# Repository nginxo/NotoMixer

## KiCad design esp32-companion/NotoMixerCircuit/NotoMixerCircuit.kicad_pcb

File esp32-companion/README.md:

# NotoMixer Companion per ESP32-S3

Firmware Arduino per ESP32-S3 N16R8 e ILI9488 SPI. Mostra entrambe le deck con titolo, BPM, tempo, stato di riproduzione, una finestra scorrevole di 8 secondi e la panoramica del brano. Le waveform arrivano da NotoMixer attraverso la porta COM USB. Le ampiezze di bassi, medi e alti sono disegnate a strati in blu, arancio e avorio. La finestra scorrevole mostra la griglia dei beat e il numero di battuta. Hot cue e loop attivi sono visibili anche nella panoramica.

## Collegamenti

| Display | ESP32-S3 |
| --- | --- |
| VDD | 3V3, se previsto dal modulo |
| GND | GND |
| CS | GPIO 10 |
| RST | GPIO 9 |
| D/C | GPIO 8 |
| SDI / MOSI | GPIO 11 |
| SCK | GPIO 12 |
| SDO / MISO | GPIO 13, facoltativo per il display in sola scrittura |
| BL | GPIO 7, attivo HIGH sul modulo provato |

Il preset riproduce il cablaggio e l'accensione dello sketch provato. GPIO 7 viene tenuto a LOW durante l'inizializzazione del pannello e portato a HIGH subito dopo. Su un modulo diverso verifica i requisiti di VDD e BL. Tutte le impostazioni del display sono in [Config.h](NotoMixerCompanion/Config.h).

Il preset usa SPI2 in modalità 0 e rotazione 1 (480 × 320 in orizzontale). Usa rotazione 3 per girare lo schermo di 180° in orizzontale. Se il tuo modulo scambia rosso e blu, prova `DisplayBgr = true`. Se inverte chiaro e scuro, prova `DisplayInverted = true`.

## Primo avvio

1. In Arduino IDE installa il core **esp32 by Espressif Systems** e, dal Gestore librerie, **LovyanGFX**.
2. Apri [NotoMixerCompanion.ino](NotoMixerCompanion/NotoMixerCompanion.ino) e seleziona **ESP32S3 Dev Module** e la porta della scheda.
3. Imposta i valori qui sotto, compila e carica lo sketch. All'avvio appare il logo di NotoMixer. Il display torna al logo quando la connessione si chiude o smette di ricevere dati.

| Opzione Arduino IDE | Valore |
| --- | --- |
| CPU Frequency | 240 MHz |
| Flash Size | 16MB (128Mb) |
| Flash Mode | QIO 80MHz |
| PSRAM | OPI PSRAM |
| USB CDC On Boot | Enabled |
| USB Mode | Hardware CDC and JTAG |
| Upload Mode | UART0 / Hardware CDC |
| Upload Speed | 460800 se disponibile, altrimenti 115200 |
| Partition Scheme | Default 4MB with spiffs |

## Collegamento a NotoMixer

1. Collega l'ESP32 via USB e chiudi il Monitor seriale di Arduino IDE per liberare la porta COM.
2. Avvia la versione aggiornata di NotoMixer presente in questo repository. Usa il collegamento COM già presente nell'app. Su questo PC il bridge **CH343** è comparso come **COM5**.
3. Quando lo schermo mostra le deck A e B, carica un brano e prova play, pausa e un salto sulla timeline. I picchi compaiono quando l'analisi del brano li rende disponibili.

Il preset usa il bridge **CH343** su UART0 a **115200 baud**. Se colleghi invece la porta USB nativa dell'ESP32-S3, abilita **USB CDC On Boot** e imposta `CompanionUseNativeUsb = true` in `Config.h` prima di ricompilare.

## Browser dei brani

Con la companion collegata e la finestra di NotoMixer attiva, premi **Alt+B** per aprire la libreria sul display. Usa **↑ / ↓** per scegliere il brano, **1** o **2** per caricarlo sulla deck corrispondente ed **Esc** per tornare alle waveform. In alto compare `AVAILABLE SONGS (D:\)` con l'unità della libreria. Il contatore a destra mostra l'ultimo brano della pagina rispetto al totale, per esempio `8/42`. La lista mostra titolo, BPM e durata quando disponibili.

Per comandare lo stesso browser via COM, invia una riga `BROWSER:OPEN`, `BROWSER:UP`, `BROWSER:DOWN`, `BROWSER:LOAD1`, `BROWSER:LOAD2` o `BROWSER:CLOSE`. Il firmware inoltra l'azione a NotoMixer come `NM-BROWSER:<azione>`. I comandi inviati da un secondo programma richiedono un collegamento seriale che consenta lo scambio con NotoMixer, dato che l'app occupa la porta COM.

NotoMixer invia la pagina al display come `NM-LIBRARY:` seguito da Base64. I primi 12 byte contengono lo stato aperto, il numero di righe, la selezione nella pagina, un byte riservato, il totale e l'indice della prima riga. Totale e indice sono uint32 little-endian. Ogni riga contiene 80 byte di titolo UTF-8, BPM in decimi e durata in secondi, entrambi uint16 little-endian. Dalla versione 7 seguono 32 byte con l'unità della libreria in UTF-8 terminato da NUL.

## Protocollo

La companion si identifica con la riga `NM-COMPANION:7`. NotoMixer risponde con righe `NM-WAVEFORM:` seguite dai dati in Base64. Il pacchetto ha sigla `NM05`, due record di stato da 148 byte in ordine A, B e i picchi delle sole deck aggiornate. Gli aggiornamenti di posizione occupano 300 byte. Tutti i campi numerici multibyte sono little-endian. L'app accetta anche i firmware precedenti.

NotoMixer invia i picchi quando la companion si identifica o quando cambiano. Invia una sola waveform per pacchetto, fino a 6000 campioni. Durante il caricamento può svuotare una deck con il solo record di stato.

| Offset nel record | Campo |
| --- | --- |
| 0 | Flag. Bit 0 brano caricato, bit 1 riproduzione, bit 2 picchi a tre bande, bit 3 loop attivo, bit 4 sostituzione dei picchi, bit 5 avviso di fine brano, bit 6 conto alla rovescia EndSync sulla deck entrante, bit 7 transizione EndSync in corso sulla deck uscente |
| 1 | Riservato |
| 2 | Numero di picchi, uint16 da 0 a 6000 |
| 4, 8, 12, 16 | Posizione in secondi, durata in secondi, velocità di avanzamento, BPM. Quattro float32 |
| 20 | Titolo UTF-8, 80 byte con terminazione NUL |
| 100, 104, 108, 112 | BPM sorgente, offset della griglia, inizio e fine del loop. Quattro float32 |
| 116 | Otto tempi hot cue come float32. -1 indica un cue assente |

Dopo i due record arrivano i picchi delle deck con bit 4 attivo. Con il bit 2 attivo ogni campione contiene tre ampiezze in un uint16: bassi nei bit 11–15, medi nei bit 5–10 e alti nei bit 0–4. Per l'inviluppo in attesa dell'analisi o per l'audio di test si usa un byte per campione.

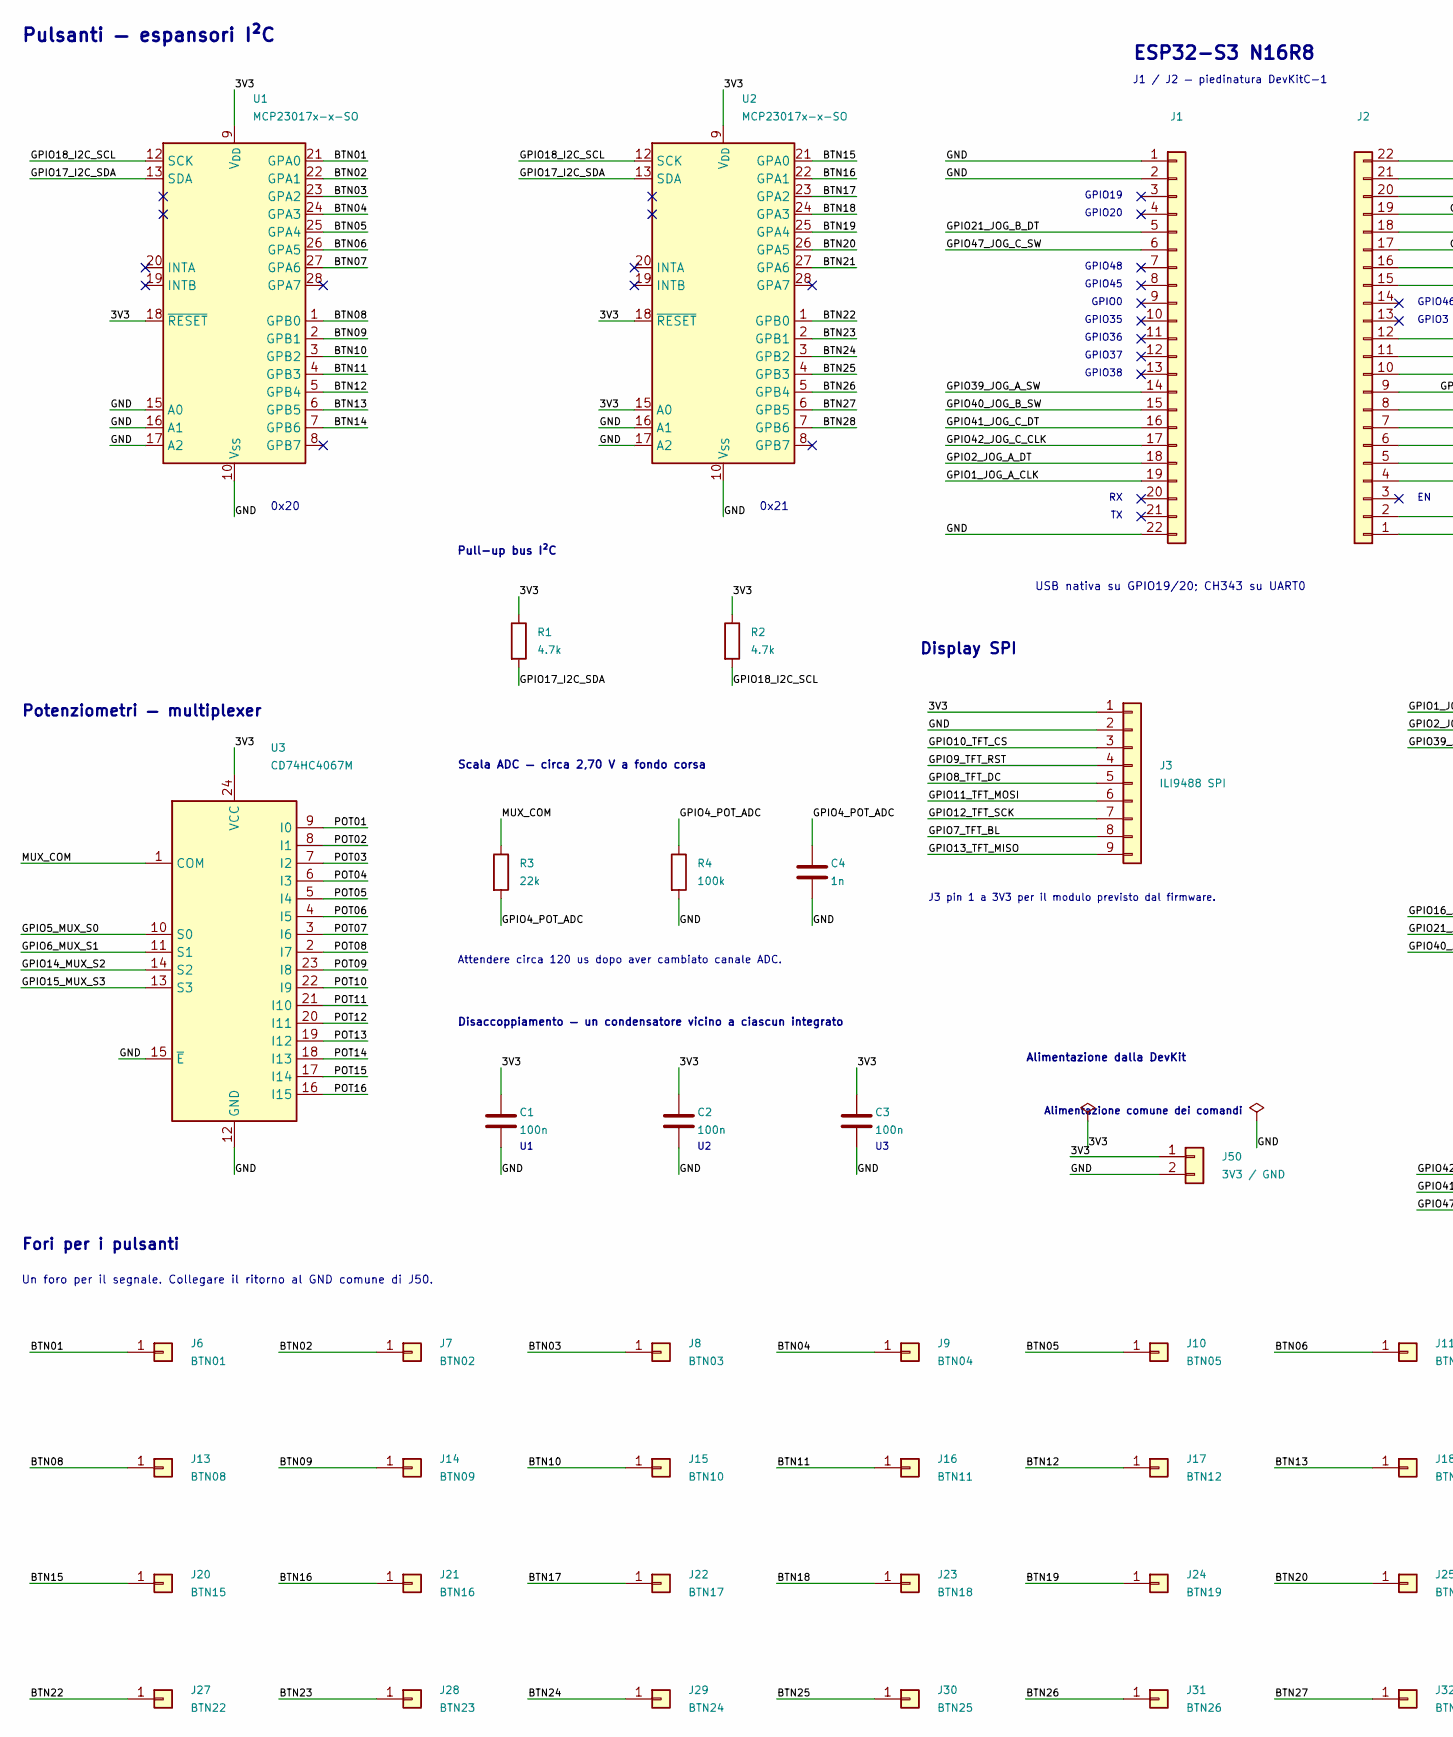
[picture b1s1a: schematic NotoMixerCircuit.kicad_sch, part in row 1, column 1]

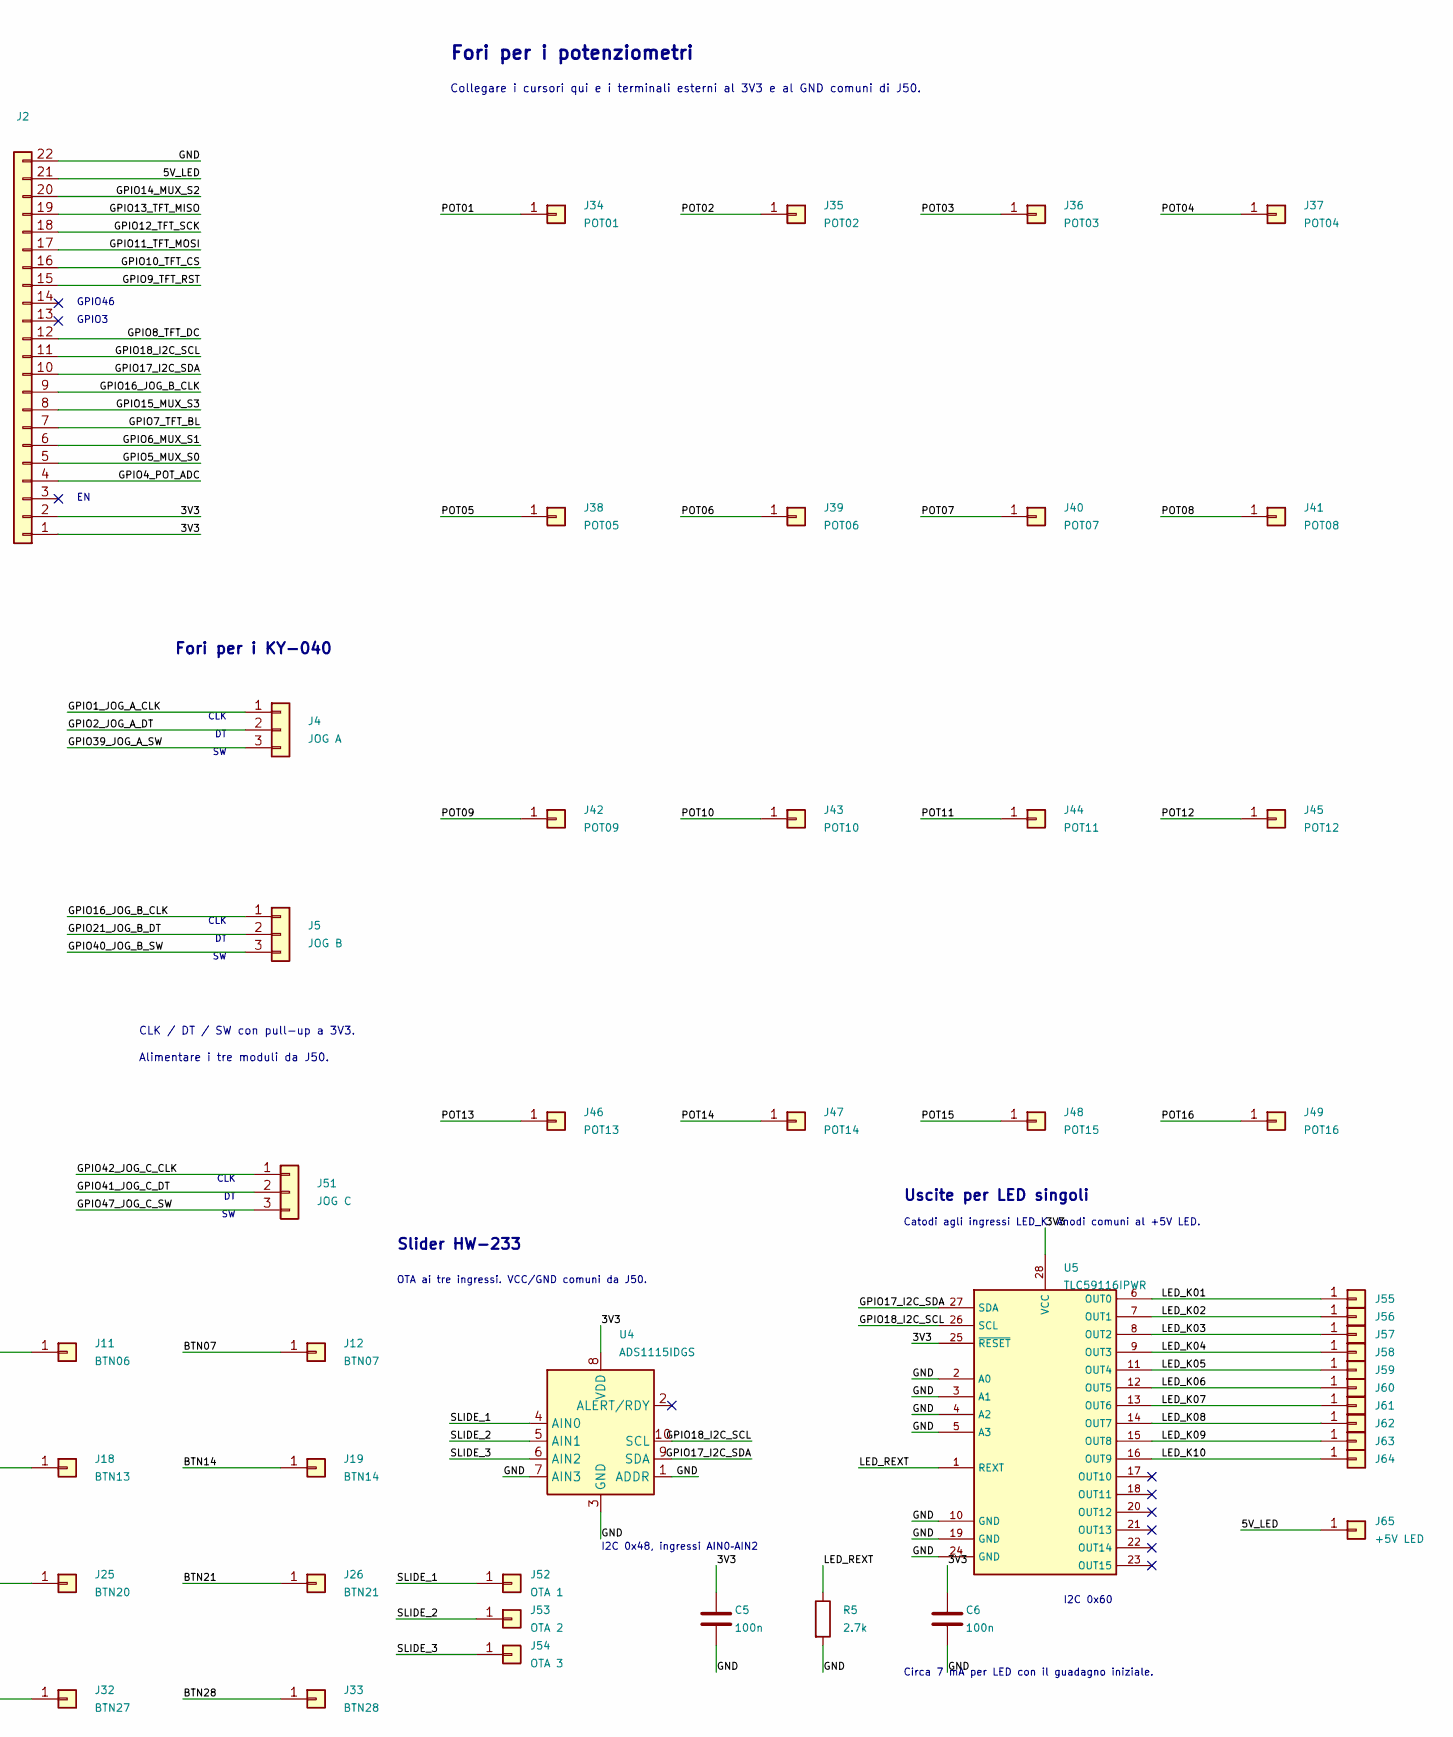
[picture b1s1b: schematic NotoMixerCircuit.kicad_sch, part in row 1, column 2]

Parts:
C1, C2, C3, C5, C6: 100n; C_Disc_D5.0mm_W2.5mm_P2.50mm
C4: 1n; C_Disc_D5.0mm_W2.5mm_P2.50mm
J1, J2: ESP32-S3; PinSocket_1x22_P2.54mm_Vertical
J3: ILI9488 SPI; PinHeader_1x09_P2.54mm_Vertical
J4: JOG A; SolderWire-0.5sqmm_1x03_P4.8mm_D0.9mm_OD2.3mm
J5: JOG B; SolderWire-0.5sqmm_1x03_P4.8mm_D0.9mm_OD2.3mm
J6: BTN01; SolderWire-0.5sqmm_1x01_D0.9mm_OD2.3mm
J7: BTN02; SolderWire-0.5sqmm_1x01_D0.9mm_OD2.3mm
J8: BTN03; SolderWire-0.5sqmm_1x01_D0.9mm_OD2.3mm
J9: BTN04; SolderWire-0.5sqmm_1x01_D0.9mm_OD2.3mm
J10: BTN05; SolderWire-0.5sqmm_1x01_D0.9mm_OD2.3mm
J11: BTN06; SolderWire-0.5sqmm_1x01_D0.9mm_OD2.3mm
J12: BTN07; SolderWire-0.5sqmm_1x01_D0.9mm_OD2.3mm
J13: BTN08; SolderWire-0.5sqmm_1x01_D0.9mm_OD2.3mm
J14: BTN09; SolderWire-0.5sqmm_1x01_D0.9mm_OD2.3mm
J15: BTN10; SolderWire-0.5sqmm_1x01_D0.9mm_OD2.3mm
J16: BTN11; SolderWire-0.5sqmm_1x01_D0.9mm_OD2.3mm
J17: BTN12; SolderWire-0.5sqmm_1x01_D0.9mm_OD2.3mm
J18: BTN13; SolderWire-0.5sqmm_1x01_D0.9mm_OD2.3mm
J19: BTN14; SolderWire-0.5sqmm_1x01_D0.9mm_OD2.3mm
J20: BTN15; SolderWire-0.5sqmm_1x01_D0.9mm_OD2.3mm
J21: BTN16; SolderWire-0.5sqmm_1x01_D0.9mm_OD2.3mm
J22: BTN17; SolderWire-0.5sqmm_1x01_D0.9mm_OD2.3mm
J23: BTN18; SolderWire-0.5sqmm_1x01_D0.9mm_OD2.3mm
J24: BTN19; SolderWire-0.5sqmm_1x01_D0.9mm_OD2.3mm
J25: BTN20; SolderWire-0.5sqmm_1x01_D0.9mm_OD2.3mm
J26: BTN21; SolderWire-0.5sqmm_1x01_D0.9mm_OD2.3mm
J27: BTN22; SolderWire-0.5sqmm_1x01_D0.9mm_OD2.3mm
J28: BTN23; SolderWire-0.5sqmm_1x01_D0.9mm_OD2.3mm
J29: BTN24; SolderWire-0.5sqmm_1x01_D0.9mm_OD2.3mm
J30: BTN25; SolderWire-0.5sqmm_1x01_D0.9mm_OD2.3mm
J31: BTN26; SolderWire-0.5sqmm_1x01_D0.9mm_OD2.3mm
J32: BTN27; SolderWire-0.5sqmm_1x01_D0.9mm_OD2.3mm
J33: BTN28; SolderWire-0.5sqmm_1x01_D0.9mm_OD2.3mm
J34: POT01; SolderWire-0.5sqmm_1x01_D0.9mm_OD2.3mm
J35: POT02; SolderWire-0.5sqmm_1x01_D0.9mm_OD2.3mm
J36: POT03; SolderWire-0.5sqmm_1x01_D0.9mm_OD2.3mm
J37: POT04; SolderWire-0.5sqmm_1x01_D0.9mm_OD2.3mm
J38: POT05; SolderWire-0.5sqmm_1x01_D0.9mm_OD2.3mm
J39: POT06; SolderWire-0.5sqmm_1x01_D0.9mm_OD2.3mm
J40: POT07; SolderWire-0.5sqmm_1x01_D0.9mm_OD2.3mm
J41: POT08; SolderWire-0.5sqmm_1x01_D0.9mm_OD2.3mm
J42: POT09; SolderWire-0.5sqmm_1x01_D0.9mm_OD2.3mm
J43: POT10; SolderWire-0.5sqmm_1x01_D0.9mm_OD2.3mm
J44: POT11; SolderWire-0.5sqmm_1x01_D0.9mm_OD2.3mm
J45: POT12; SolderWire-0.5sqmm_1x01_D0.9mm_OD2.3mm
J46: POT13; SolderWire-0.5sqmm_1x01_D0.9mm_OD2.3mm
J47: POT14; SolderWire-0.5sqmm_1x01_D0.9mm_OD2.3mm
J48: POT15; SolderWire-0.5sqmm_1x01_D0.9mm_OD2.3mm
J49: POT16; SolderWire-0.5sqmm_1x01_D0.9mm_OD2.3mm
J50: 3V3 / GND; SolderWire-0.5sqmm_1x02_P4.8mm_D0.9mm_OD2.3mm
J51: JOG C; SolderWire-0.5sqmm_1x03_P4.8mm_D0.9mm_OD2.3mm
J52: OTA 1; SolderWire-0.5sqmm_1x01_D0.9mm_OD2.3mm
J53: OTA 2; SolderWire-0.5sqmm_1x01_D0.9mm_OD2.3mm
J54: OTA 3; SolderWire-0.5sqmm_1x01_D0.9mm_OD2.3mm
J55: K01; SolderWire_D1.15mm_OD1.5mm
J56: K02; SolderWire_D1.15mm_OD1.5mm
J57: K03; SolderWire_D1.15mm_OD1.5mm
J58: K04; SolderWire_D1.15mm_OD1.5mm
J59: K05; SolderWire_D1.15mm_OD1.5mm
J60: K06; SolderWire_D1.15mm_OD1.5mm
J61: K07; SolderWire_D1.15mm_OD1.5mm
J62: K08; SolderWire_D1.15mm_OD1.5mm
J63: K09; SolderWire_D1.15mm_OD1.5mm
J64: K10; SolderWire_D1.15mm_OD1.5mm
J65: +5V LED; SolderWire-0.5sqmm_1x01_D0.9mm_OD2.3mm
R1, R2: 4.7k; R_Axial_DIN0207_L6.3mm_D2.5mm_P7.62mm_Horizontal
R3: 22k; R_Axial_DIN0207_L6.3mm_D2.5mm_P7.62mm_Horizontal
R4: 100k; R_Axial_DIN0207_L6.3mm_D2.5mm_P7.62mm_Horizontal
R5: 2.7k; R_Axial_DIN0207_L6.3mm_D2.5mm_P7.62mm_Horizontal
U1, U2: MCP23017x-x-SO; SOIC-28W_7.5x17.9mm_P1.27mm
U3: CD74HC4067M; SOIC-24W_7.5x15.4mm_P1.27mm
U4: ADS1115IDGS; TSSOP-10_3x3mm_P0.5mm
U5: TLC59116IPWR; TSSOP-28_4.4x9.7mm_P0.65mm

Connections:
/3V3: C1.1, C2.1, C3.1, C5.1, C6.1, J2.1, J2.2, J3.1, J50.1, R1.1, R2.1, U1.9 (V_{DD}), U1.18 (~RESET), U2.9 (V_{DD}), U2.15 (A0), U2.18 (~RESET), U3.24 (VCC), U4.8 (VDD), U5.25 (~RESET), U5.28 (VCC)
/5V_LED: J2.21, J65.1
/BTN01: J6.1 (Pin_1_1), U1.21 (GPA0)
/BTN02: J7.1 (Pin_1_1), U1.22 (GPA1)
/BTN03: J8.1 (Pin_1_1), U1.23 (GPA2)
/BTN04: J9.1 (Pin_1_1), U1.24 (GPA3)
/BTN05: J10.1 (Pin_1_1), U1.25 (GPA4)
/BTN06: J11.1 (Pin_1_1), U1.26 (GPA5)
/BTN07: J12.1 (Pin_1_1), U1.27 (GPA6)
/BTN08: J13.1 (Pin_1_1), U1.1 (GPB0)
/BTN09: J14.1 (Pin_1_1), U1.2 (GPB1)
/BTN10: J15.1 (Pin_1_1), U1.3 (GPB2)
/BTN11: J16.1 (Pin_1_1), U1.4 (GPB3)
/BTN12: J17.1 (Pin_1_1), U1.5 (GPB4)
/BTN13: J18.1 (Pin_1_1), U1.6 (GPB5)
/BTN14: J19.1 (Pin_1_1), U1.7 (GPB6)
/BTN15: J20.1 (Pin_1_1), U2.21 (GPA0)
/BTN16: J21.1 (Pin_1_1), U2.22 (GPA1)
/BTN17: J22.1 (Pin_1_1), U2.23 (GPA2)
/BTN18: J23.1 (Pin_1_1), U2.24 (GPA3)
/BTN19: J24.1 (Pin_1_1), U2.25 (GPA4)
/BTN20: J25.1 (Pin_1_1), U2.26 (GPA5)
/BTN21: J26.1 (Pin_1_1), U2.27 (GPA6)
/BTN22: J27.1 (Pin_1_1), U2.1 (GPB0)
/BTN23: J28.1 (Pin_1_1), U2.2 (GPB1)
/BTN24: J29.1 (Pin_1_1), U2.3 (GPB2)
/BTN25: J30.1 (Pin_1_1), U2.4 (GPB3)
/BTN26: J31.1 (Pin_1_1), U2.5 (GPB4)
/BTN27: J32.1 (Pin_1_1), U2.6 (GPB5)
/BTN28: J33.1 (Pin_1_1), U2.7 (GPB6)
/GND: C1.2, C2.2, C3.2, C4.2, C5.2, C6.2, J1.1, J1.2, J1.22, J2.22, J3.2, J50.2, R4.2, R5.2, U1.10 (V_{SS}), U1.15 (A0), U1.16 (A1), U1.17 (A2), U2.10 (V_{SS}), U2.16 (A1), U2.17 (A2), U3.12 (GND), U3.15 (~E), U4.1 (ADDR), U4.3 (GND), U4.7 (AIN3), U5.2 (A0), U5.3 (A1), U5.4 (A2), U5.5 (A3), U5.10 (GND), U5.19 (GND), U5.24 (GND)
/GPIO1_JOG_A_CLK: J1.19, J4.1
/GPIO2_JOG_A_DT: J1.18, J4.2
/GPIO4_POT_ADC: C4.1, J2.4, R3.2, R4.1
/GPIO5_MUX_S0: J2.5, U3.10 (S0)
/GPIO6_MUX_S1: J2.6, U3.11 (S1)
/GPIO7_TFT_BL: J2.7, J3.8
/GPIO8_TFT_DC: J2.12, J3.5
/GPIO9_TFT_RST: J2.15, J3.4
/GPIO10_TFT_CS: J2.16, J3.3
/GPIO11_TFT_MOSI: J2.17, J3.6
/GPIO12_TFT_SCK: J2.18, J3.7
/GPIO13_TFT_MISO: J2.19, J3.9
/GPIO14_MUX_S2: J2.20, U3.14 (S2)
/GPIO15_MUX_S3: J2.8, U3.13 (S3)
/GPIO16_JOG_B_CLK: J2.9, J5.1
/GPIO17_I2C_SDA: J2.10, R1.2, U1.13 (SDA), U2.13 (SDA), U4.9 (SDA), U5.27 (SDA)
/GPIO18_I2C_SCL: J2.11, R2.2, U1.12 (SCK), U2.12 (SCK), U4.10 (SCL), U5.26 (SCL)
/GPIO21_JOG_B_DT: J1.5, J5.2
/GPIO39_JOG_A_SW: J1.14, J4.3
/GPIO40_JOG_B_SW: J1.15, J5.3
/GPIO41_JOG_C_DT: J1.16, J51.2
/GPIO42_JOG_C_CLK: J1.17, J51.1
/GPIO47_JOG_C_SW: J1.6, J51.3
/LED_K01: J55.1, U5.6 (OUT0)
/LED_K02: J56.1, U5.7 (OUT1)
/LED_K03: J57.1, U5.8 (OUT2)
/LED_K04: J58.1, U5.9 (OUT3)
/LED_K05: J59.1, U5.11 (OUT4)
/LED_K06: J60.1, U5.12 (OUT5)
/LED_K07: J61.1, U5.13 (OUT6)
/LED_K08: J62.1, U5.14 (OUT7)
/LED_K09: J63.1, U5.15 (OUT8)
/LED_K10: J64.1, U5.16 (OUT9)
/LED_REXT: R5.1, U5.1 (REXT)
/MUX_COM: R3.1, U3.1 (COM)
/POT01: J34.1 (Pin_1_1), U3.9 (I0)
/POT02: J35.1 (Pin_1_1), U3.8 (I1)
/POT03: J36.1 (Pin_1_1), U3.7 (I2)
/POT04: J37.1 (Pin_1_1), U3.6 (I3)
/POT05: J38.1 (Pin_1_1), U3.5 (I4)
/POT06: J39.1 (Pin_1_1), U3.4 (I5)
/POT07: J40.1 (Pin_1_1), U3.3 (I6)
/POT08: J41.1 (Pin_1_1), U3.2 (I7)
/POT09: J42.1 (Pin_1_1), U3.23 (I8)
/POT10: J43.1 (Pin_1_1), U3.22 (I9)
/POT11: J44.1 (Pin_1_1), U3.21 (I10)
/POT12: J45.1 (Pin_1_1), U3.20 (I11)
/POT13: J46.1 (Pin_1_1), U3.19 (I12)
/POT14: J47.1 (Pin_1_1), U3.18 (I13)
/POT15: J48.1 (Pin_1_1), U3.17 (I14)
/POT16: J49.1 (Pin_1_1), U3.16 (I15)
/SLIDE_1: J52.1, U4.4 (AIN0)
/SLIDE_2: J53.1, U4.5 (AIN1)
/SLIDE_3: J54.1, U4.6 (AIN2)

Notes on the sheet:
Fori per i pulsanti
USB nativa su GPIO19/20; CH343 su UART0
Un foro per il segnale. Collegare il ritorno al GND comune di J50.
GPIO19
GPIO38
GPIO36
GPIO48
GPIO35
Fori per i KY-040
GPIO0
Collegare i cursori qui e i terminali esterni al 3V3 e al GND comuni di J50.
Slider HW-233
Fori per i potenziometri
OTA ai tre ingressi. VCC/GND comuni da J50.
Pull-up bus I²C
Display SPI
0x20
CLK
GPIO46
J1 / J2 — piedinatura DevKitC-1
GPIO20
Uscite per LED singoli
GPIO3
Catodi agli ingressi LED_K. Anodi comuni al +5V LED.
Scala ADC — circa 2,70 V a fondo corsa
I2C 0x60
Attendere circa 120 us dopo aver cambiato canale ADC.
ESP32-S3 N16R8
GPIO45
J3 pin 1 a 3V3 per il modulo previsto dal firmware.
Circa 7 mA per LED con il guadagno iniziale.
I2C 0x48, ingressi AIN0–AIN2
Alimentazione dalla DevKit
Alimentare i tre moduli da J50.
Pulsanti — espansori I²C
Alimentazione comune dei comandi
0x21
GPIO37
Disaccoppiamento — un condensatore vicino a ciascun integrato
CLK / DT / SW con pull-up a 3V3.

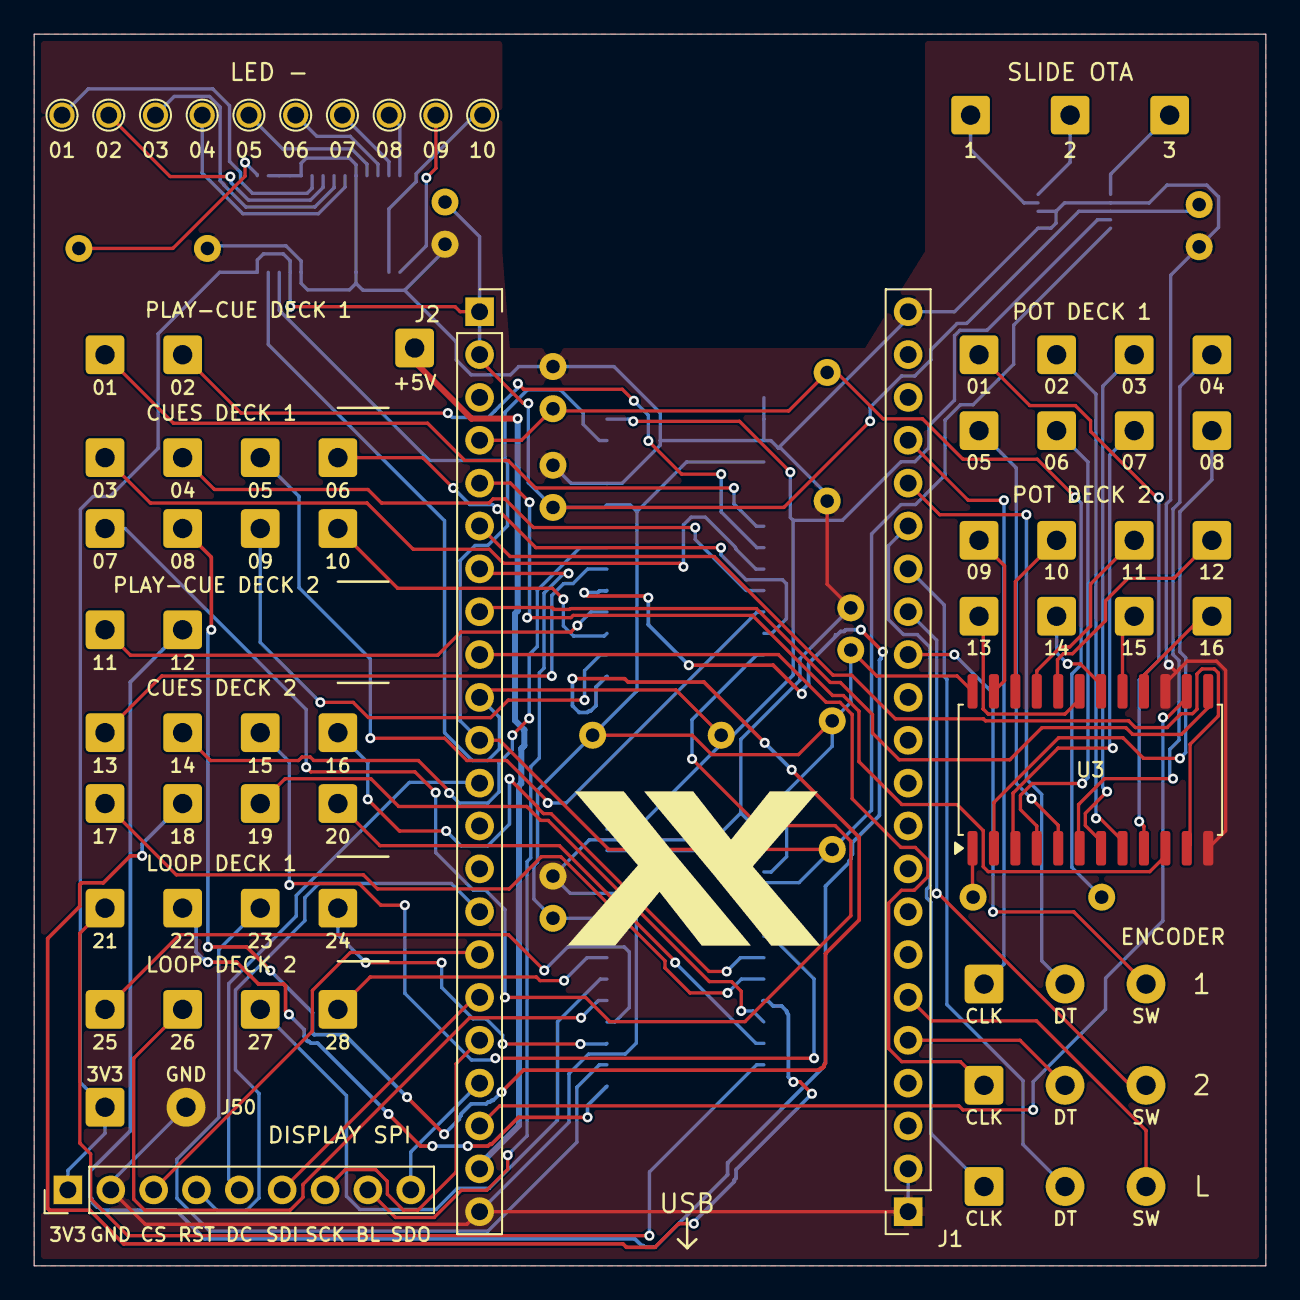
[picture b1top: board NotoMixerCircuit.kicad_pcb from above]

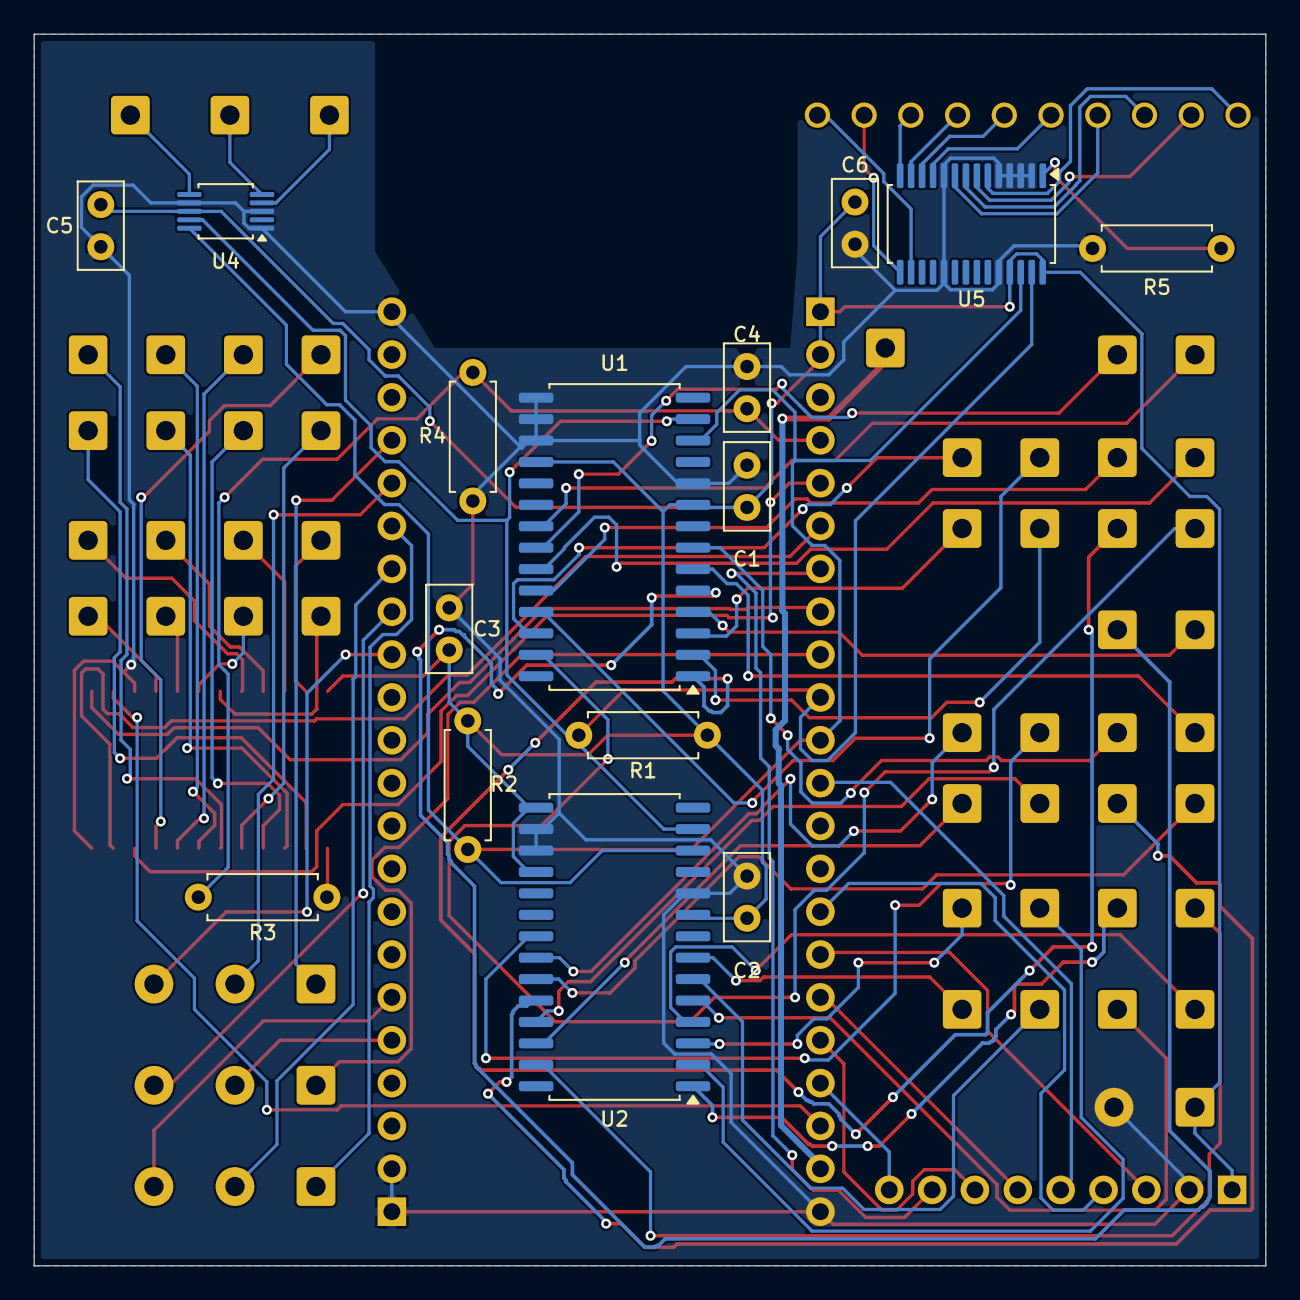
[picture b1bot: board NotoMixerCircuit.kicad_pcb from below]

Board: 2 copper layers, 73.0 x 73.0 mm, 81 parts (15 on the bottom side), 85 nets.
